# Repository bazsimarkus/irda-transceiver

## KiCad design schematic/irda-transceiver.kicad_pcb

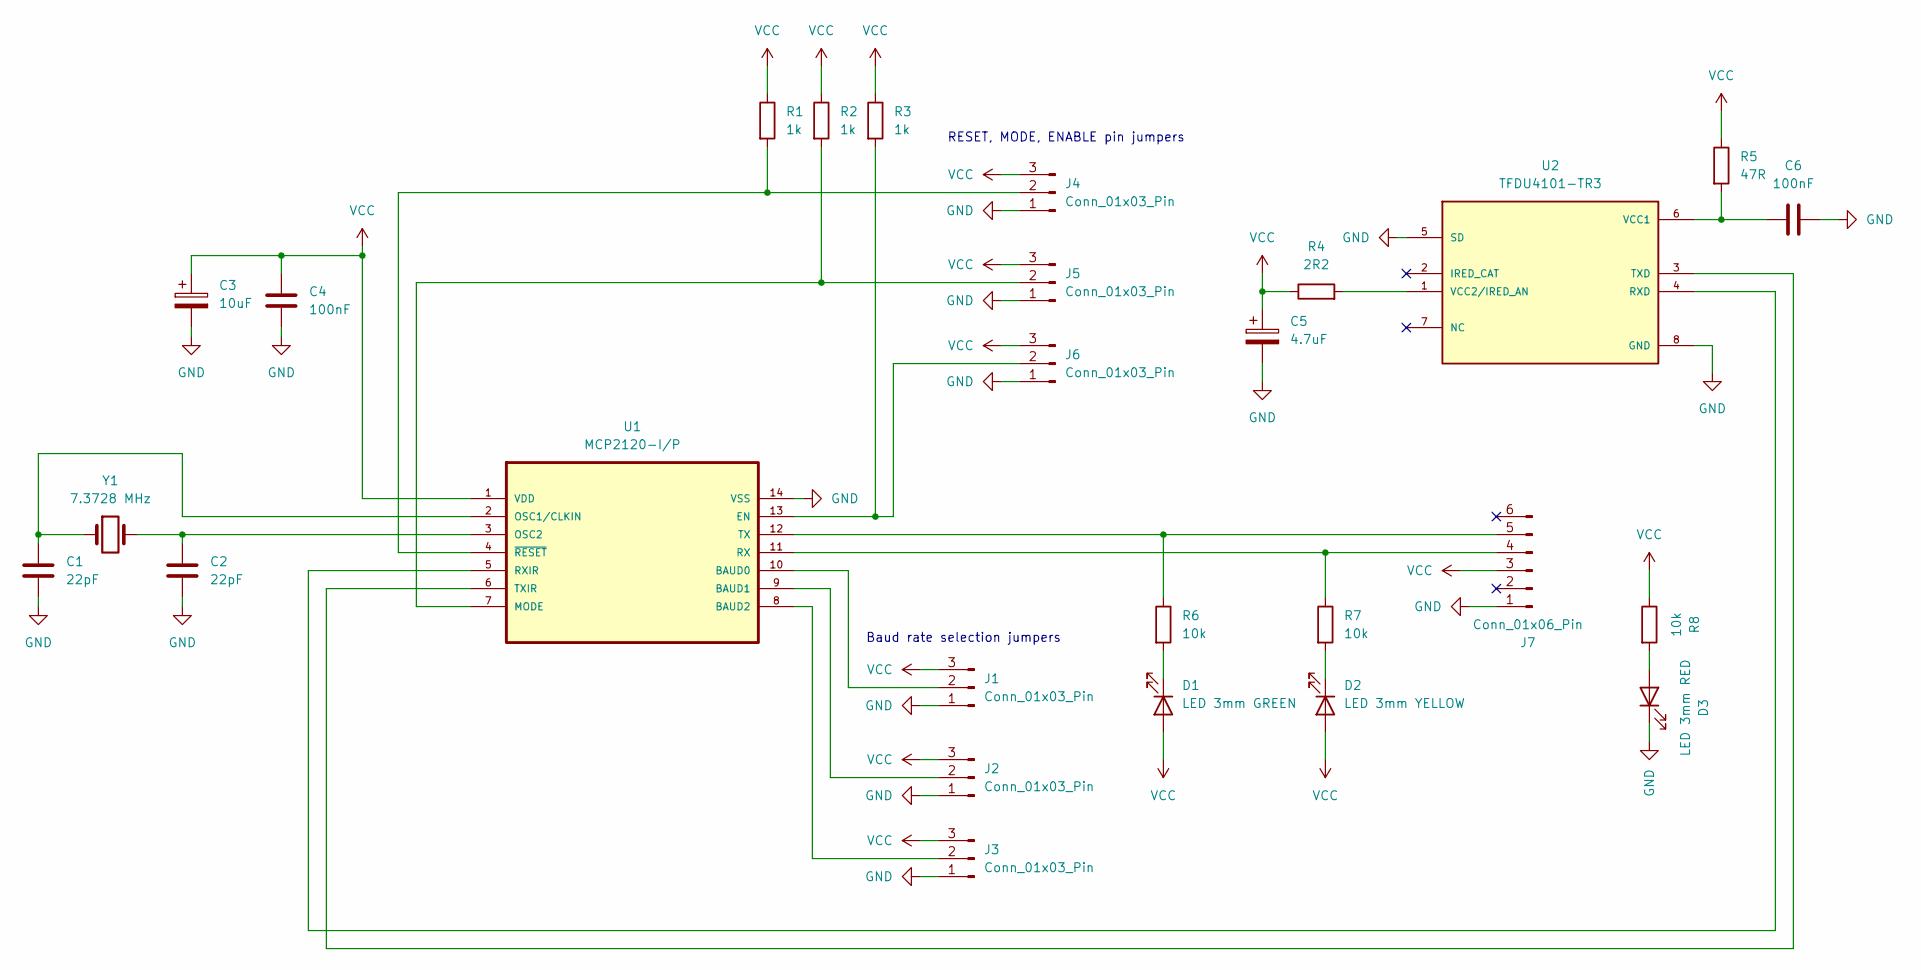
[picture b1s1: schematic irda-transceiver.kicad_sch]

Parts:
C1, C2: 22pF; C_Rect_L4.6mm_W2.0mm_P2.50mm_MKS02_FKP02
C3: 10uF; CP_Radial_D4.0mm_P2.00mm
C4, C6: 100nF; C_100nF_L7.0mm_W2.5mm_P5.00mm
C5: 4.7uF; CP_Radial_D4.0mm_P2.00mm
D1: LED 3mm GREEN; LED_D3.0mm_GREEN
D2: LED 3mm YELLOW; LED_D3.0mm_YELLOW
D3: LED 3mm RED; LED_D3.0mm_RED
J1, J2, J3, J4, J5, J6: Conn_01x03_Pin; PinHeader_1x03_P2.54mm_Vertical
J7: Conn_01x06_Pin; PinHeader_1x06_P2.54mm_Vertical
R1, R2, R3: 1k; R_1k_Axial_DIN0207
R4: 2R2; R_1k_Axial_DIN0207
R5: 47R; R_1k_Axial_DIN0207
R6, R7, R8: 10k; R_470_Axial_DIN0207
U1: MCP2120-I/P; DIP-14_W7.62mm; MPN MCP2120-I/P
U2: TFDU4101-TR3; PARTREV 2.4
Y1: 7.3728 MHz; Crystal_HC49-U_Vertical

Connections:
GND: C1.2, C2.2, C3.2, C4.1, C5.2, C6.2, D3.1 (K), J1.1, J2.1, J3.1, J4.1, J5.1, J6.1, J7.1, U1.14 (VSS), U2.5 (SD), U2.8 (GND)
unnamed: D1.1 (K), R6.2
unnamed: D2.1 (K), R7.2
unnamed: D3.2 (A), R8.2
unnamed: J1.2, U1.10 (BAUD0)
unnamed: J2.2, U1.9 (BAUD1)
unnamed: J3.2, U1.8 (BAUD2)
unnamed: J4.2, R1.2, U1.4 (~RESET)
unnamed: J5.2, R2.2, U1.7 (MODE)
unnamed: J6.2, R3.2, U1.13 (EN)
unnamed: J7.4, R7.1, U1.11 (RX)
unnamed: J7.5, R6.1, U1.12 (TX)
unnamed: C1.1, U1.2 (OSC1/CLKIN), Y1.1
unnamed: C2.1, U1.3 (OSC2), Y1.2
unnamed: U1.5 (RXIR), U2.4 (RXD)
unnamed: U1.6 (TXIR), U2.3 (TXD)
unnamed: C6.1, R5.2, U2.6 (VCC1)
unnamed: R4.2, U2.1 (VCC2/IRED_AN)
VCC: C3.1, C4.2, C5.1, D1.2 (A), D2.2 (A), J1.3, J2.3, J3.3, J4.3, J5.3, J6.3, J7.3, R1.1, R2.1, R3.1, R4.1, R5.1, R8.1, U1.1 (VDD)

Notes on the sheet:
RESET, MODE, ENABLE pin jumpers
Baud rate selection jumpers

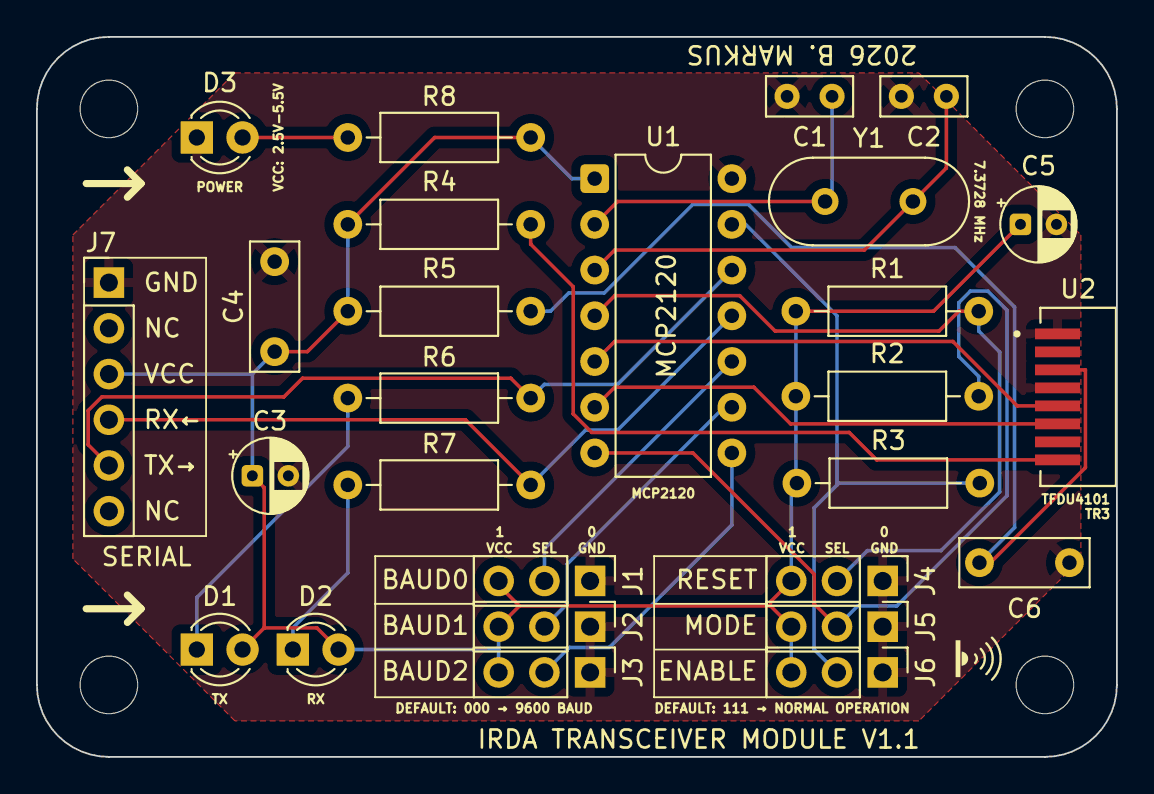
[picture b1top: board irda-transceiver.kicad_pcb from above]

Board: 2 copper layers, 60.0 x 40.0 mm, 32 parts (0 on the bottom side), 19 nets.

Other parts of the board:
G1: LOGO
MH1, MH2, MH3, MH4: MountingHole_3.2mm_M3_DIN965

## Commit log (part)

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2026-05-31 Schematic added
2026-05-31 PCB traces and silkscreen refined
